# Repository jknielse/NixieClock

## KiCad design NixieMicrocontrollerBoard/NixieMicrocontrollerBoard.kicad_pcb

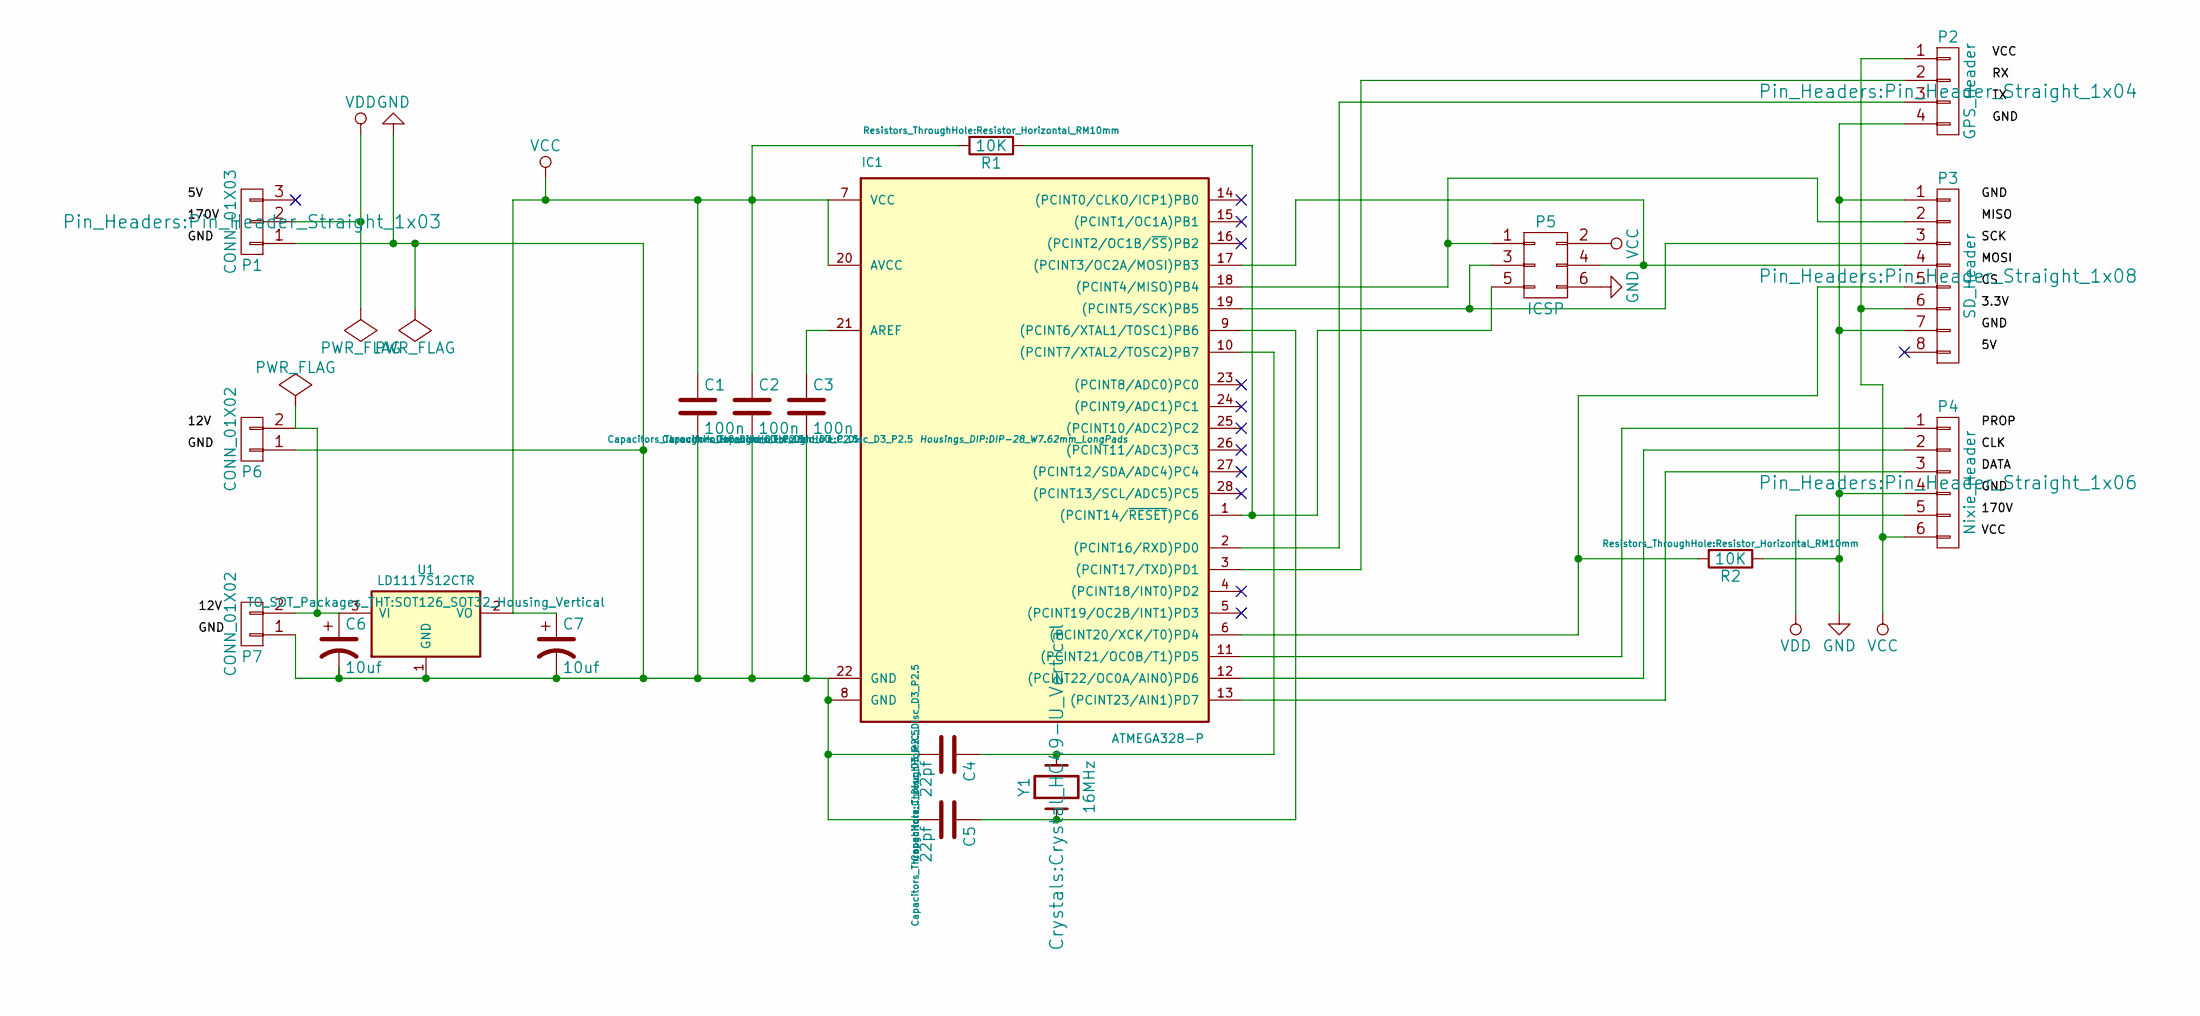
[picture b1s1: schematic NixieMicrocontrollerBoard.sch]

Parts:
C1, C2, C3: 100n; C_Disc_D3_P2.5
C4, C5: 22pf; C_Disc_D3_P2.5
C6, C7: 10uf; C_Radial_D5_L11_P2.5
IC1: ATMEGA328-P; DIP-28_W7.62mm_LongPads
P1: CONN_01X03; Pin_Header_Straight_1x03
P2: GPS_Header; Pin_Header_Straight_1x04
P3: SD_Header; Pin_Header_Straight_1x08
P4: Nixie_Header; Pin_Header_Straight_1x06
P5: ICSP; Pin_Header_Straight_2x03
P6, P7: CONN_01X02; Pin_Header_Straight_1x02
R1, R2: 10K; Resistor_Horizontal_RM10mm
U1: LD1117S12CTR; SOT126_SOT32_Housing_Vertical
Y1: 16MHz; Crystal_HC49-U_Vertical

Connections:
GND: C1.2, C2.2, C3.2, C4.2, C5.2, C6.2, C7.2, IC1.8 (GND), IC1.22 (GND), P1.1, P2.4, P3.1, P3.7, P4.4, P5.6, P6.1, P7.1, R2.1, U1.1 (GND)
unnamed: C3.1, IC1.21 (AREF)
unnamed: C4.1, IC1.10 ((PCINT7/XTAL2/TOSC2)PB7), Y1.2
unnamed: C5.1, IC1.9 ((PCINT6/XTAL1/TOSC1)PB6), Y1.1
unnamed: C6.1, P6.2, P7.2, U1.3 (VI)
unnamed: IC1.1 ((PCINT14/~RESET~)PC6), P5.5, R1.1
unnamed: IC1.2 ((PCINT16/RXD)PD0), P2.3
unnamed: IC1.3 ((PCINT17/TXD)PD1), P2.2
unnamed: IC1.6 ((PCINT20/XCK/T0)PD4), P3.5, R2.2
unnamed: IC1.11 ((PCINT21/OC0B/T1)PD5), P4.1
unnamed: IC1.12 ((PCINT22/OC0A/AIN0)PD6), P4.2
unnamed: IC1.13 ((PCINT23/AIN1)PD7), P4.3
unnamed: IC1.17 ((PCINT3/OC2A/MOSI)PB3), P3.4, P5.4
unnamed: IC1.18 ((PCINT4/MISO)PB4), P3.2, P5.1
unnamed: IC1.19 ((PCINT5/SCK)PB5), P3.3, P5.3
VCC: C1.1, C2.1, C7.1, IC1.7 (VCC), IC1.20 (AVCC), P2.1, P3.6, P4.6, P5.2, R1.2, U1.2 (VO)
VDD: P1.2, P4.5

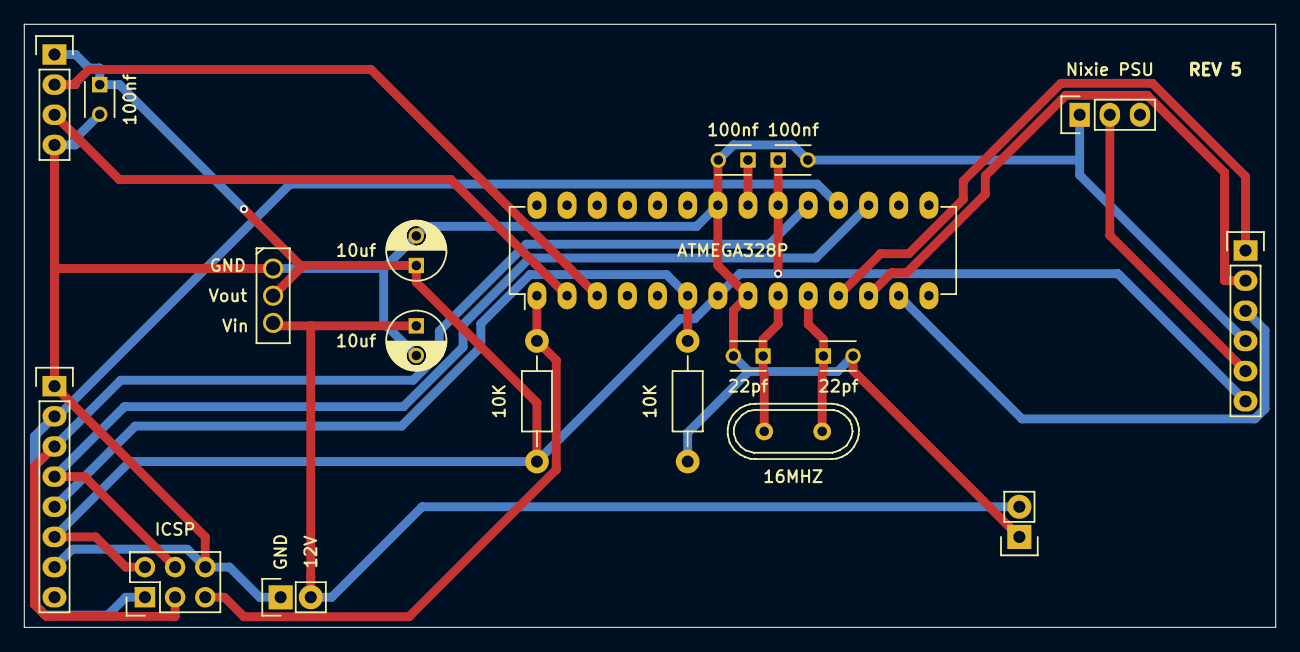
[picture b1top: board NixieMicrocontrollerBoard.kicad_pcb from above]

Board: 2 copper layers, 105.4 x 50.8 mm, 19 parts (0 on the bottom side), 17 nets.

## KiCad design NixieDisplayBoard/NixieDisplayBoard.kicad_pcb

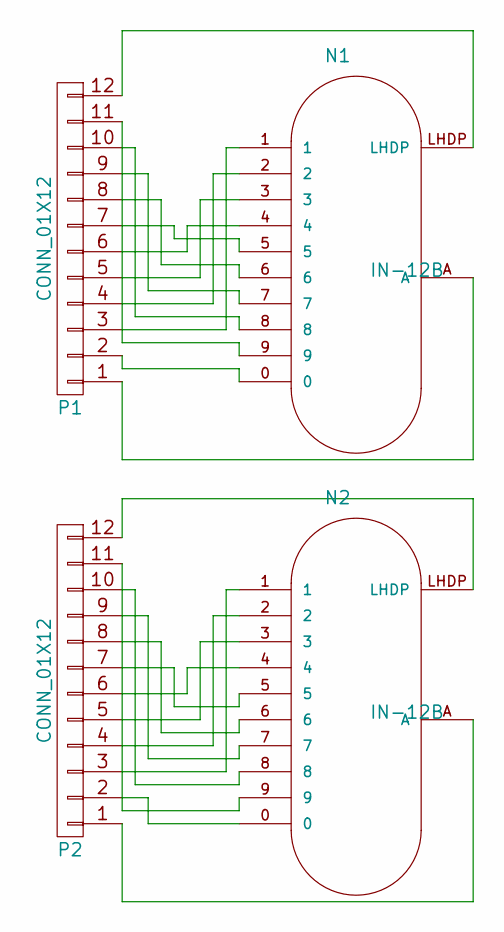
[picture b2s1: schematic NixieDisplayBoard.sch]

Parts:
N1, N2: IN-12B; russian-nixies-IN-12
P1, P2: CONN_01X12; Pin_Header_Straight_1x12

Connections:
unnamed: N1.0, P1.2
unnamed: N1.1, P1.3
unnamed: N1.2, P1.4
unnamed: N1.3, P1.5
unnamed: N1.4, P1.6
unnamed: N1.5, P1.7
unnamed: N1.6, P1.8
unnamed: N1.7, P1.9
unnamed: N1.8, P1.10
unnamed: N1.9, P1.11
unnamed: N1.A, P1.1
unnamed: N1.LHDP, P1.12
unnamed: N2.0, P2.2
unnamed: N2.1, P2.3
unnamed: N2.2, P2.4
unnamed: N2.3, P2.5
unnamed: N2.4, P2.6
unnamed: N2.5, P2.7
unnamed: N2.6, P2.8
unnamed: N2.7, P2.9
unnamed: N2.8, P2.10
unnamed: N2.9, P2.11
unnamed: N2.A, P2.1
unnamed: N2.LHDP, P2.12

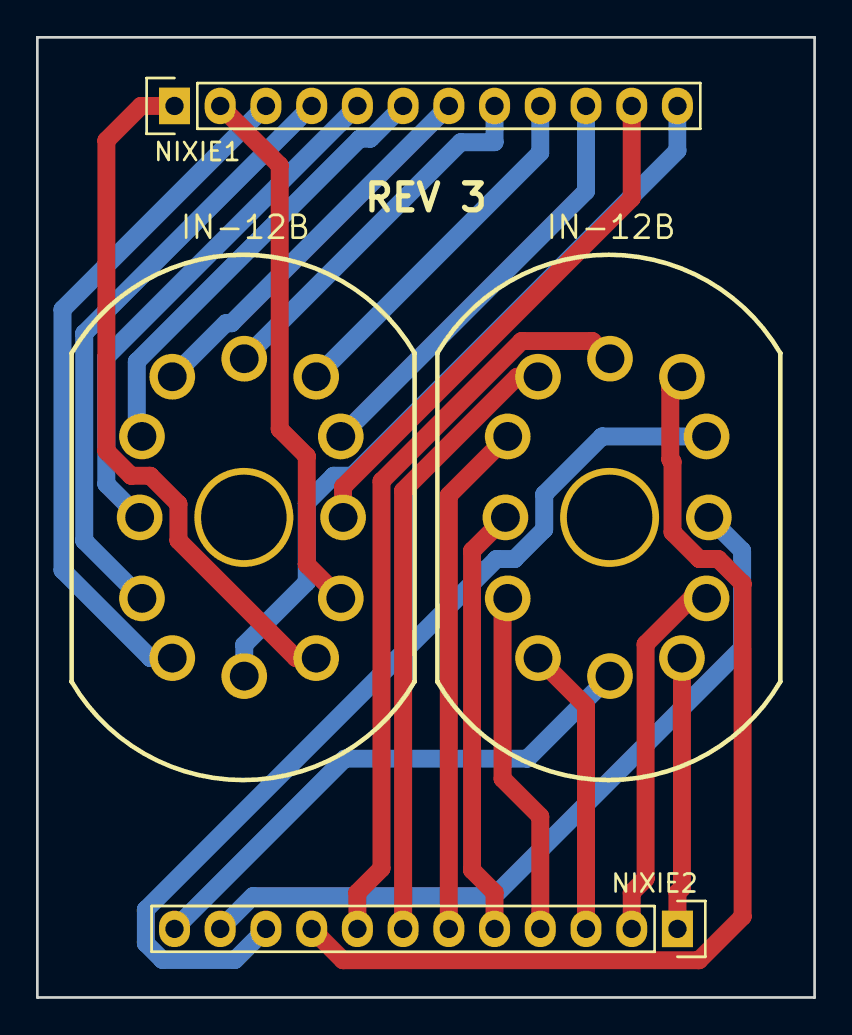
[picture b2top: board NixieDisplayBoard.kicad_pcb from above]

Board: 2 copper layers, 43.2 x 53.3 mm, 4 parts (0 on the bottom side), 24 nets.

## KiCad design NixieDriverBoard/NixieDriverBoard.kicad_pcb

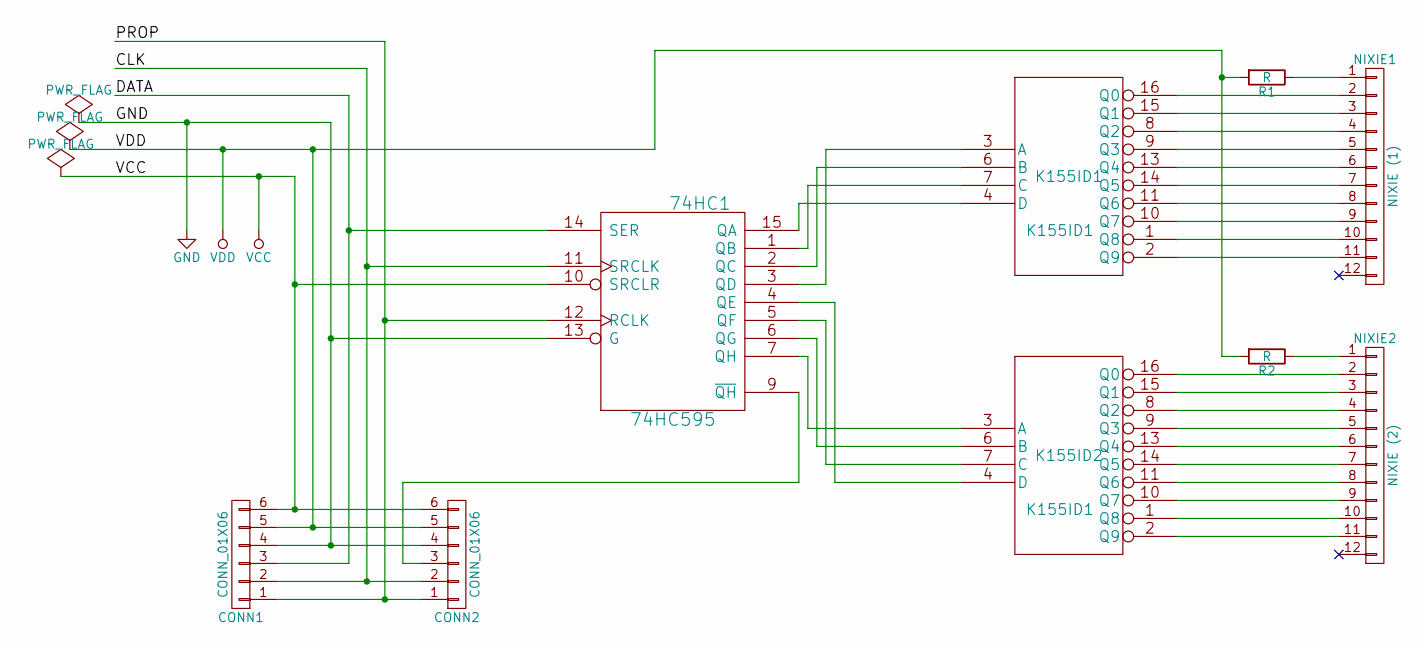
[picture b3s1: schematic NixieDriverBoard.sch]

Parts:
74HC1: 74HC595; DIP-16_W7.62mm_LongPads
CONN1, CONN2: CONN_01X06; Socket_Strip_Angled_1x06
K155ID1, K155ID2: K155ID1; DIP-16_W7.62mm_LongPads
NIXIE1: NIXIE (1); Socket_Strip_Straight_1x12
NIXIE2: NIXIE (2); Socket_Strip_Straight_1x12
R1, R2: R; Resistor_Horizontal_RM15mm

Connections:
/CLK: 74HC1.11 (SRCLK), CONN1.2, CONN2.2
/DATA: 74HC1.14 (SER), CONN1.3
/PROP: 74HC1.12 (RCLK), CONN1.1, CONN2.1
GND: 74HC1.8 (GND), 74HC1.13 (G), CONN1.4, CONN2.4, K155ID1.12 (GND), K155ID2.12 (GND)
unnamed: 74HC1.1 (QB), K155ID1.7 (C)
unnamed: 74HC1.2 (QC), K155ID1.6 (B)
unnamed: 74HC1.3 (QD), K155ID1.3 (A)
unnamed: 74HC1.4 (QE), K155ID2.4 (D)
unnamed: 74HC1.5 (QF), K155ID2.7 (C)
unnamed: 74HC1.6 (QG), K155ID2.6 (B)
unnamed: 74HC1.7 (QH), K155ID2.3 (A)
unnamed: 74HC1.9 (~QH), CONN2.3
unnamed: 74HC1.15 (QA), K155ID1.4 (D)
unnamed: K155ID1.1 (Q8), NIXIE1.10
unnamed: K155ID1.2 (Q9), NIXIE1.11
unnamed: K155ID1.8 (Q2), NIXIE1.4
unnamed: K155ID1.9 (Q3), NIXIE1.5
unnamed: K155ID1.10 (Q7), NIXIE1.9
unnamed: K155ID1.11 (Q6), NIXIE1.8
unnamed: K155ID1.13 (Q4), NIXIE1.6
unnamed: K155ID1.14 (Q5), NIXIE1.7
unnamed: K155ID1.15 (Q1), NIXIE1.3
unnamed: K155ID1.16 (Q0), NIXIE1.2
unnamed: K155ID2.1 (Q8), NIXIE2.10
unnamed: K155ID2.2 (Q9), NIXIE2.11
unnamed: K155ID2.8 (Q2), NIXIE2.4
unnamed: K155ID2.9 (Q3), NIXIE2.5
unnamed: K155ID2.10 (Q7), NIXIE2.9
unnamed: K155ID2.11 (Q6), NIXIE2.8
unnamed: K155ID2.13 (Q4), NIXIE2.6
unnamed: K155ID2.14 (Q5), NIXIE2.7
unnamed: K155ID2.15 (Q1), NIXIE2.3
unnamed: K155ID2.16 (Q0), NIXIE2.2
unnamed: NIXIE1.1, R1.1
unnamed: NIXIE2.1, R2.1
VCC: 74HC1.10 (SRCLR), 74HC1.16 (VCC), CONN1.6, CONN2.6, K155ID1.5 (VCC), K155ID2.5 (VCC)
VDD: CONN1.5, CONN2.5, R1.2, R2.2

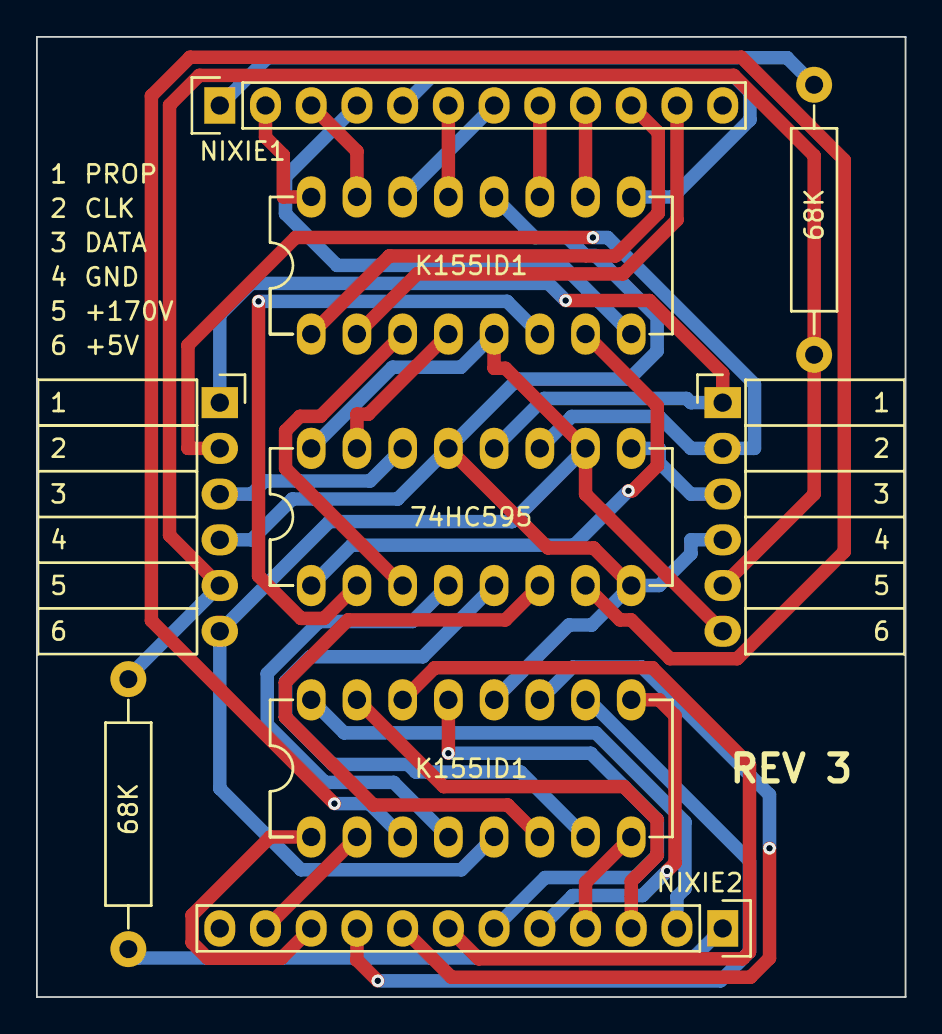
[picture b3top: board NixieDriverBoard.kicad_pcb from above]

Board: 2 copper layers, 48.3 x 53.3 mm, 9 parts (1 on the bottom side), 37 nets.

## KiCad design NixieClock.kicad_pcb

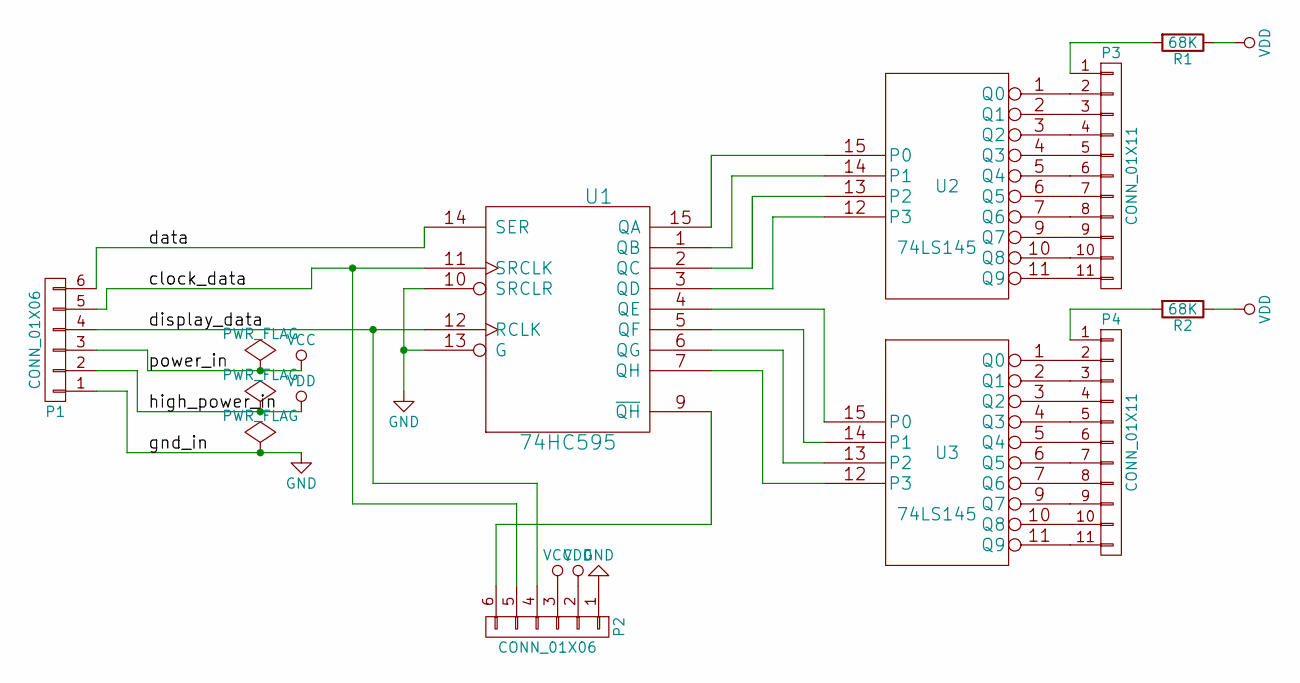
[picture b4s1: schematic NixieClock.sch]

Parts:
P1, P2: CONN_01X06; Socket_Strip_Angled_1x06
P3, P4: CONN_01X11; Socket_Strip_Straight_1x11
R1, R2: 68K; Resistor_Horizontal_RM15mm
U1: 74HC595; DIP-16_W7.62mm_LongPads
U2, U3: 74LS145; DIP-16_W7.62mm_LongPads

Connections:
/clock_data: P1.5, P2.5, U1.11 (SRCLK)
/data: P1.6, U1.14 (SER)
/display_data: P1.4, P2.4, U1.12 (RCLK)
GND: P1.1, P2.1, U1.8 (GND), U1.10 (SRCLR), U1.13 (G), U2.8 (GND), U3.8 (GND)
unnamed: P2.6, U1.9 (~QH)
unnamed: P3.1, R1.2
unnamed: P3.2, U2.1 (Q0)
unnamed: P3.3, U2.2 (Q1)
unnamed: P3.4, U2.3 (Q2)
unnamed: P3.5, U2.4 (Q3)
unnamed: P3.6, U2.5 (Q4)
unnamed: P3.7, U2.6 (Q5)
unnamed: P3.8, U2.7 (Q6)
unnamed: P3.9, U2.9 (Q7)
unnamed: P3.10, U2.10 (Q8)
unnamed: P3.11, U2.11 (Q9)
unnamed: P4.1, R2.2
unnamed: P4.2, U3.1 (Q0)
unnamed: P4.3, U3.2 (Q1)
unnamed: P4.4, U3.3 (Q2)
unnamed: P4.5, U3.4 (Q3)
unnamed: P4.6, U3.5 (Q4)
unnamed: P4.7, U3.6 (Q5)
unnamed: P4.8, U3.7 (Q6)
unnamed: P4.9, U3.9 (Q7)
unnamed: P4.10, U3.10 (Q8)
unnamed: P4.11, U3.11 (Q9)
unnamed: U1.1 (QB), U2.14 (P1)
unnamed: U1.2 (QC), U2.13 (P2)
unnamed: U1.3 (QD), U2.12 (P3)
unnamed: U1.4 (QE), U3.15 (P0)
unnamed: U1.5 (QF), U3.14 (P1)
unnamed: U1.6 (QG), U3.13 (P2)
unnamed: U1.7 (QH), U3.12 (P3)
unnamed: U1.15 (QA), U2.15 (P0)
VCC: P1.3, P2.3, U1.16 (VCC), U2.16 (VCC), U3.16 (VCC)
VDD: P1.2, P2.2, R1.1, R2.1

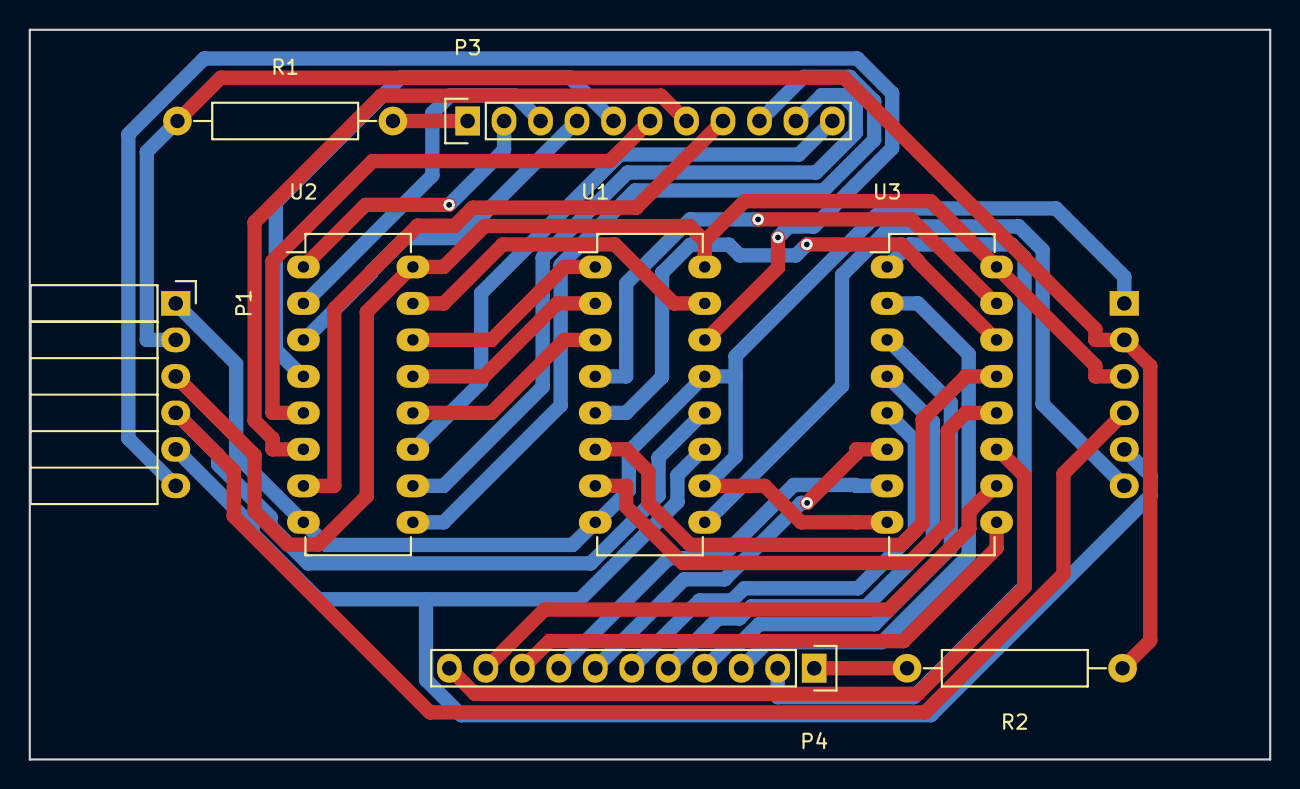
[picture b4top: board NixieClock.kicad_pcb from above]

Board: 2 copper layers, 86.4 x 50.8 mm, 9 parts (1 on the bottom side), 37 nets.

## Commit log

2015-10-18 Adds nixie tube driver circuit design
2015-11-05 Completely overhauls everything
2015-11-05 Updates the display board to center the center-hole
2015-11-21 Updates nixie boards
2015-11-21 Makes the nixie breakout board less stupid about which pins mean what...
2015-11-25 Makes driver board more intuitive, and cleans up the silkscreen layers on both boards
2015-12-02 Completes the microcontroller board
2015-12-17 Fixes up the microcontroller board, and adds a library to drive the Nixie boards
2015-12-21 Updates NixieSketch to integrate the GPS signal and the Nixie display together, and adds a test sketch just to make sure the nixies are working
2015-12-22 adds an autocalibration strategy
2015-12-23 Adds some of the timezone hashing strategy
2015-12-23 Fixes the SD card pin connections to use the SPI bus
2016-02-05 Adds python script to generate timezone information for the sd card
2016-02-06 Updates the board schematic after doing some breadboarding.. Does *not* update the gerber files
2016-02-07 Gets the sd card stuff mostly working
2016-02-08 Gets all of the timezone stuff working
2016-02-08 Adds interrupt functionality
2016-02-13 Drives the clock off of serial interrupts
2016-02-14 Makes interrupts smarter by only triggering them once per second, and tweaks the waiting animation
2016-02-14 Updates NixieMicrocontrollerBoard to include power circuits, and all of the changes I made to the breadboarded circuit yesterday
2016-02-14 Makes the board more heatsink-friendly
2016-02-18 Removes buggy-ass arduino strings
2016-02-18 Cleans up types in Timestamp clasS
2016-02-18 Cleans up types in ClockTime::setTime
2016-02-18 Reads timezone transition times as ulongs
2016-02-18 Cleans up more timestamps that should be ulongs
2016-02-18 Cleans up types in ClockTime::clockAdjustFactor
2016-02-18 Fixes types in ClockTime::unixTime
2016-02-18 Makes ClockTime::getMilliseconds return an unsigned long (as it should)
2016-02-18 removes the probably useless throttling of the timezone updates
2016-02-19 More cleaning up
2016-03-20 Fixes up NixieSketch
2016-03-27 Finally fixed the bug
2020-04-26 Removes dependency on manual interrupt registration
